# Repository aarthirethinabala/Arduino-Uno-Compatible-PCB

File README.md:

# Arduino Uno-Compatible PCB
Custom Arduino Uno-compatible PCB designed in KiCad, including schematic design, component footprint assignment, PCB layout, routing, and 3D visualization.

## Project Status
Completed

## Overview
This project involved designing an Arduino Uno-compatible printed circuit board(PCB) from the schematic stage through PCB layout and design-rule checking.
The design was created in KiCad and includes the major components and connections required for an Arduino Uno-compatible board.

## Tools Used
- KiCad
- PCB Editor
- Schematic Editor
- 3D Viewer

## Board Features
- ATmega328P microcontroller
- ATmega16U2 USB interface
- USB-C connector
- DC barrel jack input
- 5V and 3.3V voltage regulation
- Reset switch
- LEDs and indicator components
- Crystal oscillators
- ESD protection
- Resistor networks
- Through-hole and SMD components
- Front and back copper routing
- Ground copper zones

## Design Process
The PCB was developed through the following stages:
1. Schematic design
2. Electrical Rules Check(ERC)
3. Footprint assignment
4. PCB component placement
5. Board outline creation
6. Track routing
7. Via placement
8. Copper zone creation
9. Design Rules Check(DRC)
10. 3D visualization

## Current Result
The schematic and PCB layout have been completed and checked using KiCad's ERC and DRC tools.
The final design includes routed connections, vias, copper zones, and the complete board outline.

## Project Images
### Root Schematic

### Headers Schematic

### Power Schematic

### ATmega328P-PU Schematic

### PCB Layout

### 3D View

## What I Learned
- Schematic design and ERC checking
- Component footprint selection
- PCB component placement
- Routing on multiple copper layers
- Via placement
- Ground-plane/copper-zone creation
- PCB design-rule checking
- KiCad 3D visualization

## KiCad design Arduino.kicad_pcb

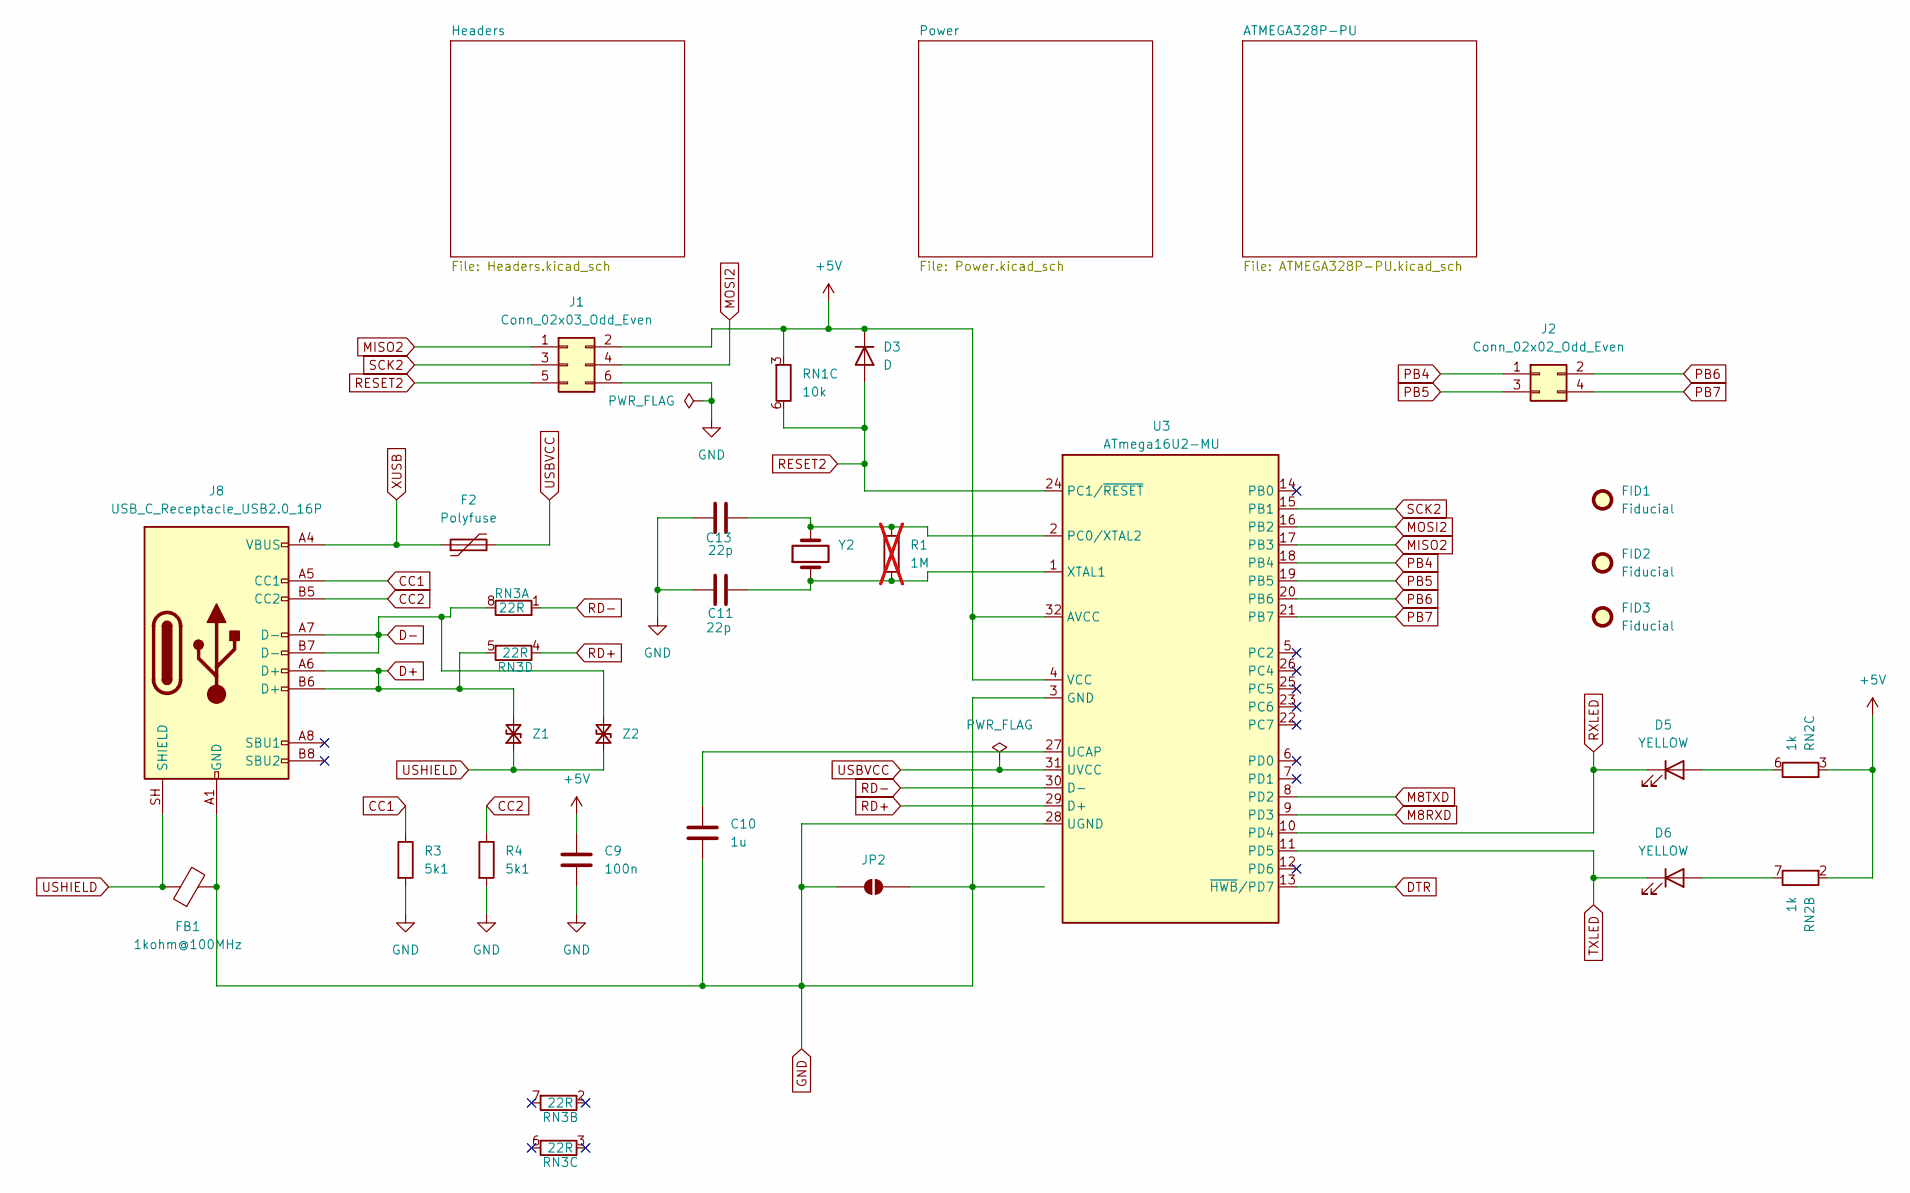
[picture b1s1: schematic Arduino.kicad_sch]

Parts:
C9: 100n; C_0603_1608Metric
C10: 1u; C_0603_1608Metric
C11, C13: 22p; C_0603_1608Metric
D3: D; D_1206_3216Metric
D5, D6: YELLOW; LED_0805_2012Metric
F2: Polyfuse; Fuse_1812_4532Metric_Pad1.30x3.40mm_HandSolder
FB1: 1kohm@100MHz; L_0805_2012Metric
FID1, FID2, FID3: Fiducial; Fiducial_1mm_Mask3mm
J1: Conn_02x03_Odd_Even; PinHeader_2x03_P2.54mm_Vertical
J2: Conn_02x02_Odd_Even; 02x02 tht hole
J8: USB_C_Receptacle_USB2.0_16P; USB_C_Receptacle_GCT_USB4105-xx-A_16P_TopMnt_Horizontal
JP2: SolderJumper_2_Open; SolderJumper-2_P1.3mm_Open_Pad1.0x1.5mm
R1: 1M; R_0603_1608Metric; not fitted
R3, R4: 5k1; R_0603_1608Metric
RN1: 10k; R_Array_Convex_4x0603
RN2: 1k; R_Array_Convex_4x0603
RN3: 22R; R_Array_Convex_4x0603
U3: ATmega16U2-MU; VQFN-32-1EP_5x5mm_P0.5mm_EP3.1x3.1mm
Y2: Crystal; Crystal_HC49-4H_Vertical
Z1, Z2: 5pF@1MHz; R_0603_1608Metric

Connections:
+5V: C9.1, D3.1 (K), J1.2, RN1.3, RN2.2, RN2.3, U3.4 (VCC), U3.32 (AVCC); also elsewhere on the board
CC1: J8.A5 (CC1), R3.1
CC2: J8.B5 (CC2), R4.1
D+: J8.A6 (D+), J8.B6 (D+), RN3.5, Z1.2 (A2)
D-: J8.A7 (D-), J8.B7 (D-), RN3.8 (R1.2), Z2.2 (A2)
DTR: U3.13 (~HWB/PD7); also elsewhere on the board
GND: C9.2, C10.2, C11.1, C13.1, FB1.2, J1.6, J8.A1 (GND), J8.A12 (GND), J8.B1 (GND), J8.B12 (GND), JP2.1 (A), JP2.2 (B), R3.2, R4.2, U3.3 (GND), U3.28 (UGND), U3.33 (GND); also elsewhere on the board
M8RXD: U3.9 (PD3); also elsewhere on the board
M8TXD: U3.8 (PD2); also elsewhere on the board
MISO2: J1.1, U3.17 (PB3)
MOSI2: J1.4, U3.16 (PB2)
unnamed: D5.2 (A), RN2.6 (R3.2)
unnamed: D6.2 (A), RN2.7 (R2.2)
unnamed: C13.2, R1.1, U3.2 (PC0/XTAL2), Y2.2
unnamed: C10.1, U3.27 (UCAP)
unnamed: C11.2, R1.2, U3.1 (XTAL1), Y2.1
PB4: J2.1, U3.18 (PB4)
PB5: J2.3, U3.19 (PB5)
PB6: J2.2, U3.20 (PB6)
PB7: J2.4, U3.21 (PB7)
RD+: RN3.4 (R4.2), U3.29 (D+)
RD-: RN3.1 (R1), U3.30 (D-)
RESET2: D3.2 (A), J1.5, RN1.6 (R3.2), U3.24 (PC1/~RESET)
RXLED: D5.1 (K), U3.10 (PD4)
SCK2: J1.3, U3.15 (PB1)
TXLED: D6.1 (K), U3.11 (PD5)
USBVCC: F2.2, U3.31 (UVCC); also elsewhere on the board
USHIELD: FB1.1, J8.SH (SHIELD), Z1.1 (A1), Z2.1 (A1)
XUSB: F2.1, J8.A4 (VBUS), J8.A9 (VBUS), J8.B4 (VBUS), J8.B9 (VBUS)

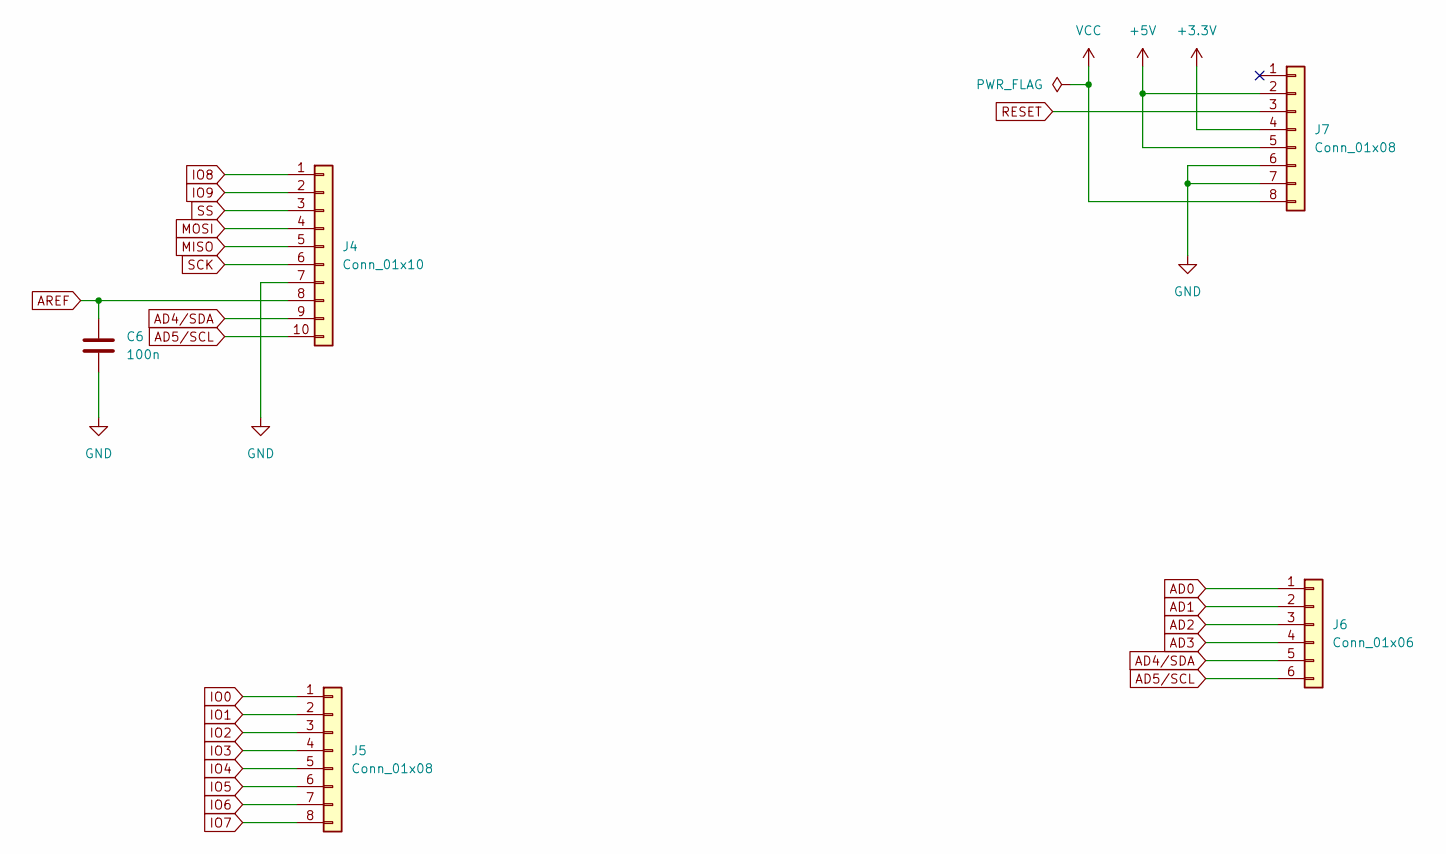
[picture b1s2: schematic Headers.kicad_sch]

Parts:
C6: 100n; C_0603_1608Metric
J4: Conn_01x10; PinSocket_1x10_P2.54mm_Vertical
J5, J7: Conn_01x08; PinSocket_1x08_P2.54mm_Vertical
J6: Conn_01x06; PinSocket_1x06_P2.54mm_Vertical

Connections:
+3.3V: J7.4; also elsewhere on the board
+5V: J7.2, J7.5; also elsewhere on the board
AD0: J6.1; also elsewhere on the board
AD1: J6.2; also elsewhere on the board
AD2: J6.3; also elsewhere on the board
AD3: J6.4; also elsewhere on the board
AD4/SDA: J4.9, J6.5; also elsewhere on the board
AD5/SCL: J4.10, J6.6; also elsewhere on the board
AREF: C6.1, J4.8; also elsewhere on the board
GND: C6.2, J4.7, J7.6, J7.7; also elsewhere on the board
IO0: J5.1; also elsewhere on the board
IO1: J5.2; also elsewhere on the board
IO2: J5.3; also elsewhere on the board
IO3: J5.4; also elsewhere on the board
IO4: J5.5; also elsewhere on the board
IO5: J5.6; also elsewhere on the board
IO6: J5.7; also elsewhere on the board
IO7: J5.8; also elsewhere on the board
IO8: J4.1; also elsewhere on the board
IO9: J4.2; also elsewhere on the board
MISO: J4.5; also elsewhere on the board
MOSI: J4.4; also elsewhere on the board
RESET: J7.3; also elsewhere on the board
SCK: J4.6; also elsewhere on the board
SS: J4.3; also elsewhere on the board
VCC: J7.8; also elsewhere on the board

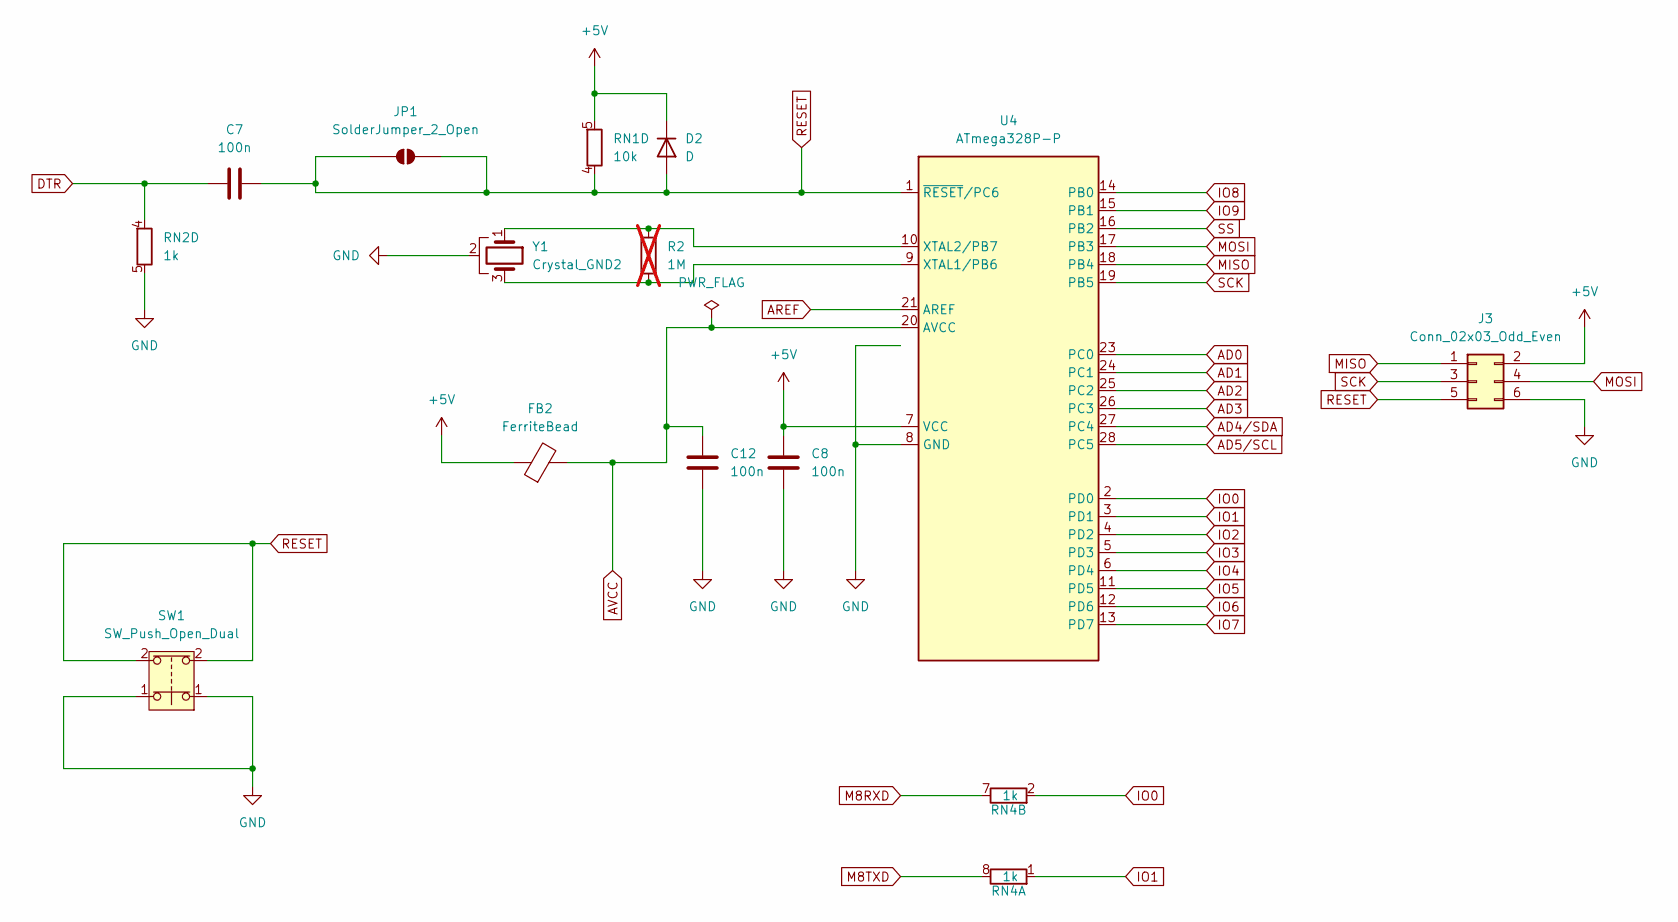
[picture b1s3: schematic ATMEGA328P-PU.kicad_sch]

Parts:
C7, C8, C12: 100n; C_0603_1608Metric
D2: D; D_1206_3216Metric
FB2: FerriteBead; L_0805_2012Metric
J3: Conn_02x03_Odd_Even; PinHeader_2x03_P2.54mm_Vertical
JP1: SolderJumper_2_Open; SolderJumper-2_P1.3mm_Open_Pad1.0x1.5mm
R2: 1M; R_0603_1608Metric; not fitted
RN1: 10k; R_Array_Convex_4x0603
RN2, RN4: 1k; R_Array_Convex_4x0603
SW1: SW_Push_Open_Dual; SW_SPST_B3S-1000
U4: ATmega328P-P; DIP-28_W7.62mm_Socket
Y1: Crystal_GND2; Resonator_SMD_Murata_CSTxExxV-3Pin_3.0x1.1mm

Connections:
+5V: C8.1, D2.1 (K), FB2.1, J3.2, RN1.5, U4.7 (VCC); also elsewhere on the board
AD0: U4.23 (PC0); also elsewhere on the board
AD1: U4.24 (PC1); also elsewhere on the board
AD2: U4.25 (PC2); also elsewhere on the board
AD3: U4.26 (PC3); also elsewhere on the board
AD4/SDA: U4.27 (PC4); also elsewhere on the board
AD5/SCL: U4.28 (PC5); also elsewhere on the board
AREF: U4.21 (AREF); also elsewhere on the board
AVCC: C12.1, FB2.2, U4.20 (AVCC)
DTR: C7.1, RN2.4 (R1); also elsewhere on the board
GND: C8.2, C12.2, J3.6, RN2.5 (R4.2), SW1.1, U4.8 (GND), U4.22 (GND), Y1.2; also elsewhere on the board
IO0: RN4.2, U4.2 (PD0); also elsewhere on the board
IO1: RN4.1 (R1), U4.3 (PD1); also elsewhere on the board
IO2: U4.4 (PD2); also elsewhere on the board
IO3: U4.5 (PD3); also elsewhere on the board
IO4: U4.6 (PD4); also elsewhere on the board
IO5: U4.11 (PD5); also elsewhere on the board
IO6: U4.12 (PD6); also elsewhere on the board
IO7: U4.13 (PD7); also elsewhere on the board
IO8: U4.14 (PB0); also elsewhere on the board
IO9: U4.15 (PB1); also elsewhere on the board
M8RXD: RN4.7 (R2.2); also elsewhere on the board
M8TXD: RN4.8 (R1.2); also elsewhere on the board
MISO: J3.1, U4.18 (PB4); also elsewhere on the board
MOSI: J3.4, U4.17 (PB3); also elsewhere on the board
unnamed: R2.2, U4.9 (XTAL1/PB6), Y1.3
unnamed: R2.1, U4.10 (XTAL2/PB7), Y1.1
RESET: C7.2, D2.2 (A), J3.5, JP1.1 (A), JP1.2 (B), RN1.4 (R4.2), SW1.2, U4.1 (~RESET/PC6); also elsewhere on the board
SCK: J3.3, U4.19 (PB5); also elsewhere on the board
SS: U4.16 (PB2); also elsewhere on the board

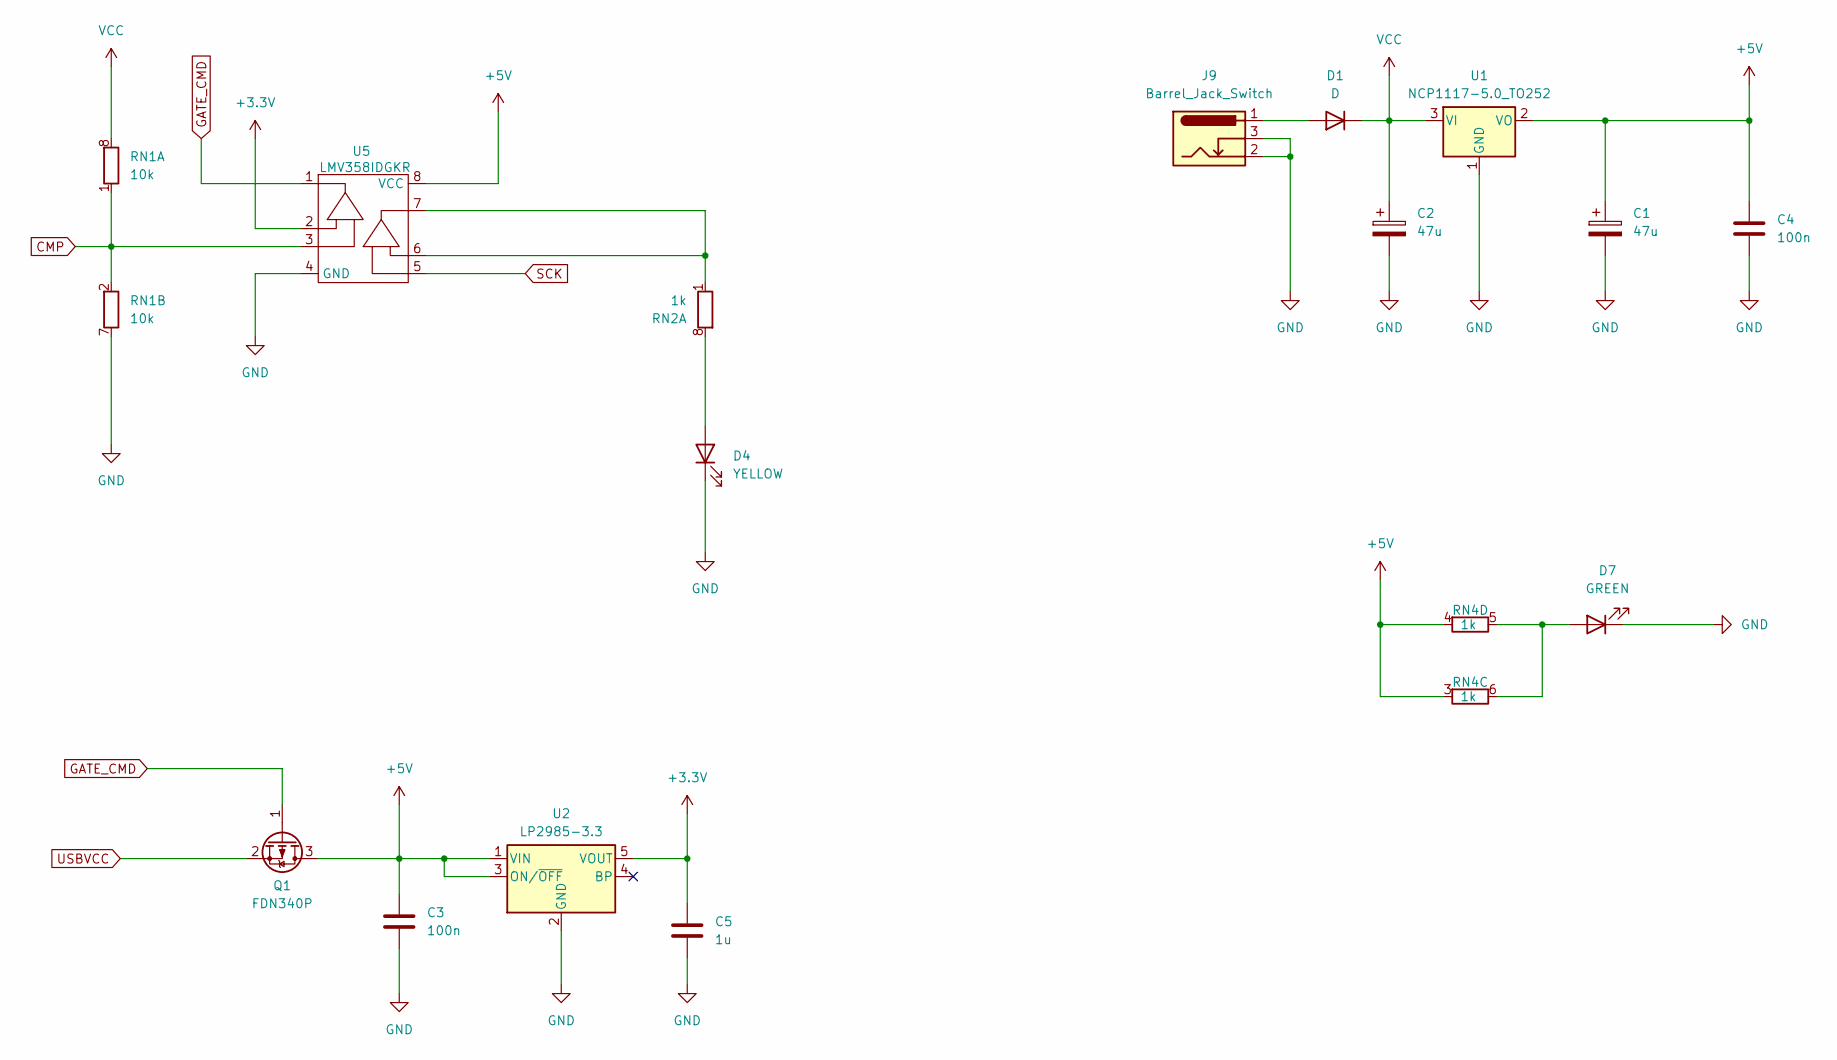
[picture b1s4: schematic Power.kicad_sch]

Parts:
C1, C2: 47u; CP_Elec_5x5.4
C3, C4: 100n; C_0603_1608Metric
C5: 1u; C_0603_1608Metric
D1: D; D_SMB
D4: YELLOW; LED_0805_2012Metric
D7: GREEN; LED_0805_2012Metric
J9: Barrel_Jack_Switch; BarrelJack_Kycon_KLDX-0202-xC_Horizontal
Q1: FDN340P; SC-59
RN1: 10k; R_Array_Convex_4x0603
RN2, RN4: 1k; R_Array_Convex_4x0603
U1: NCP1117-5.0_TO252; SOT-223-3_TabPin2
U2: LP2985-3.3; SOT-23-5
U5: LMV358IDGKR; MSOP-8_3x3mm_P0.65mm

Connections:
+3.3V: C5.1, U2.5 (VOUT), U5.2; also elsewhere on the board
+5V: C1.1, C3.1, C4.1, Q1.3 (D), RN4.3, RN4.4, U1.2 (VO), U2.1 (VIN), U2.3 (ON/~OFF), U5.8 (VCC); also elsewhere on the board
CMP: RN1.1 (R1.2), RN1.2, U5.3
GATE_CMD: Q1.1 (G), U5.1
GND: C1.2, C2.2, C3.2, C4.2, C5.2, D4.1 (K), D7.1 (K), J9.2, J9.3, RN1.7 (R2.2), U1.1 (GND), U2.2 (GND), U5.4 (GND); also elsewhere on the board
unnamed: D1.2 (A), J9.1
unnamed: D4.2 (A), RN2.8
unnamed: D7.2 (A), RN4.5 (R4.2), RN4.6 (R3.2)
unnamed: RN2.1 (R1.2), U5.6, U5.7
SCK: U5.5; also elsewhere on the board
USBVCC: Q1.2 (S); also elsewhere on the board
VCC: C2.1, D1.1 (K), RN1.8 (R1), U1.3 (VI); also elsewhere on the board

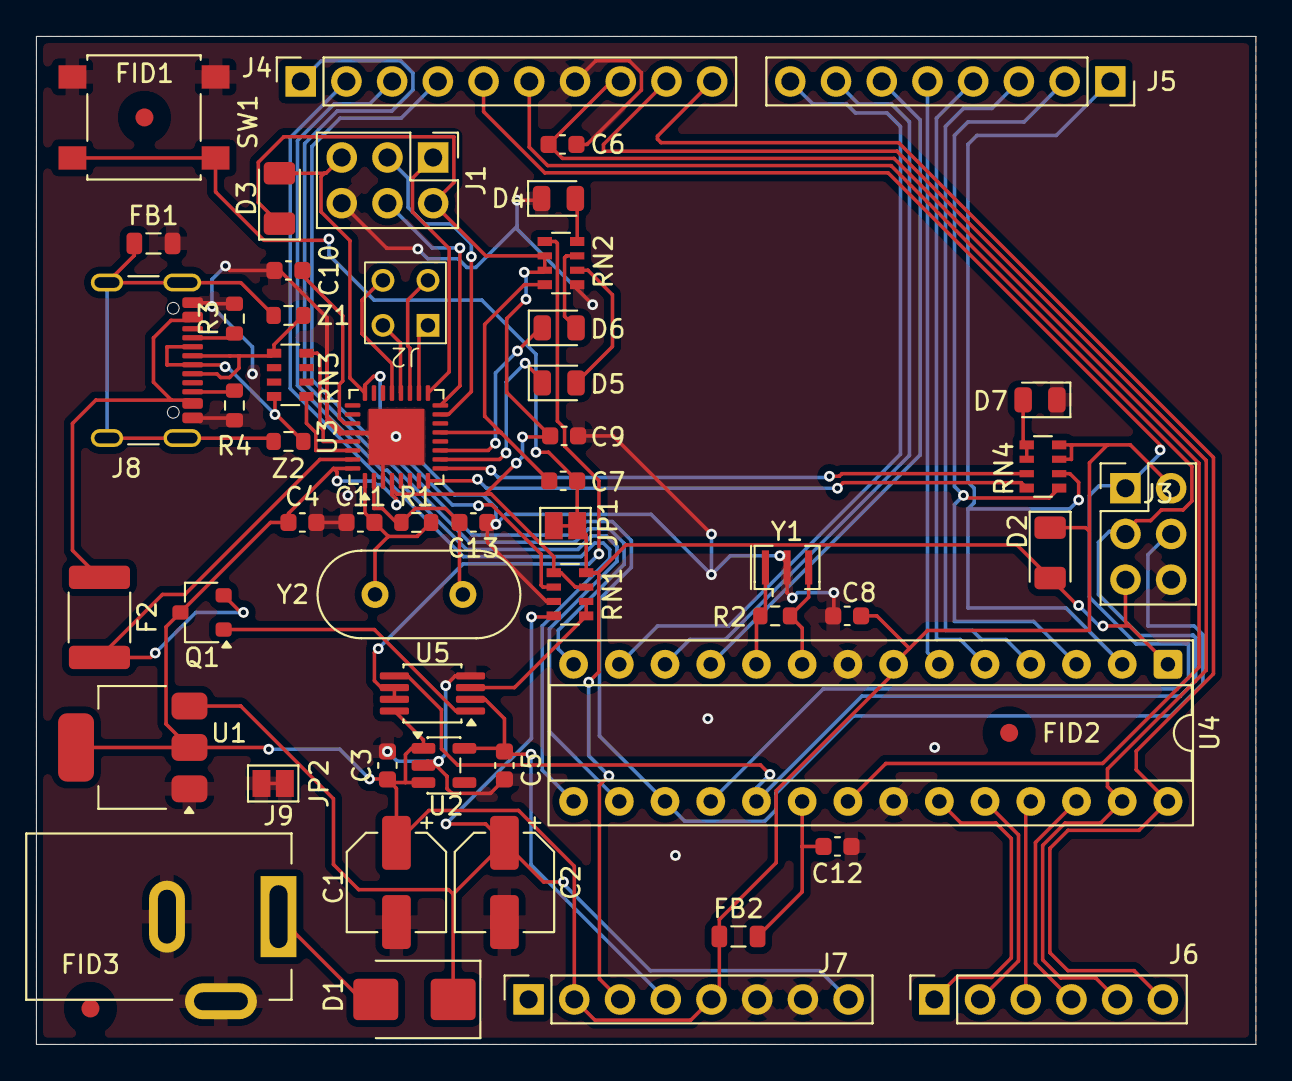
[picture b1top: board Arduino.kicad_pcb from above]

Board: 2 copper layers, 67.8 x 56.0 mm, 56 parts (0 on the bottom side), 62 nets.
